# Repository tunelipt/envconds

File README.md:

# envconds
Temperature, Pressure and Humidity measurement board and software

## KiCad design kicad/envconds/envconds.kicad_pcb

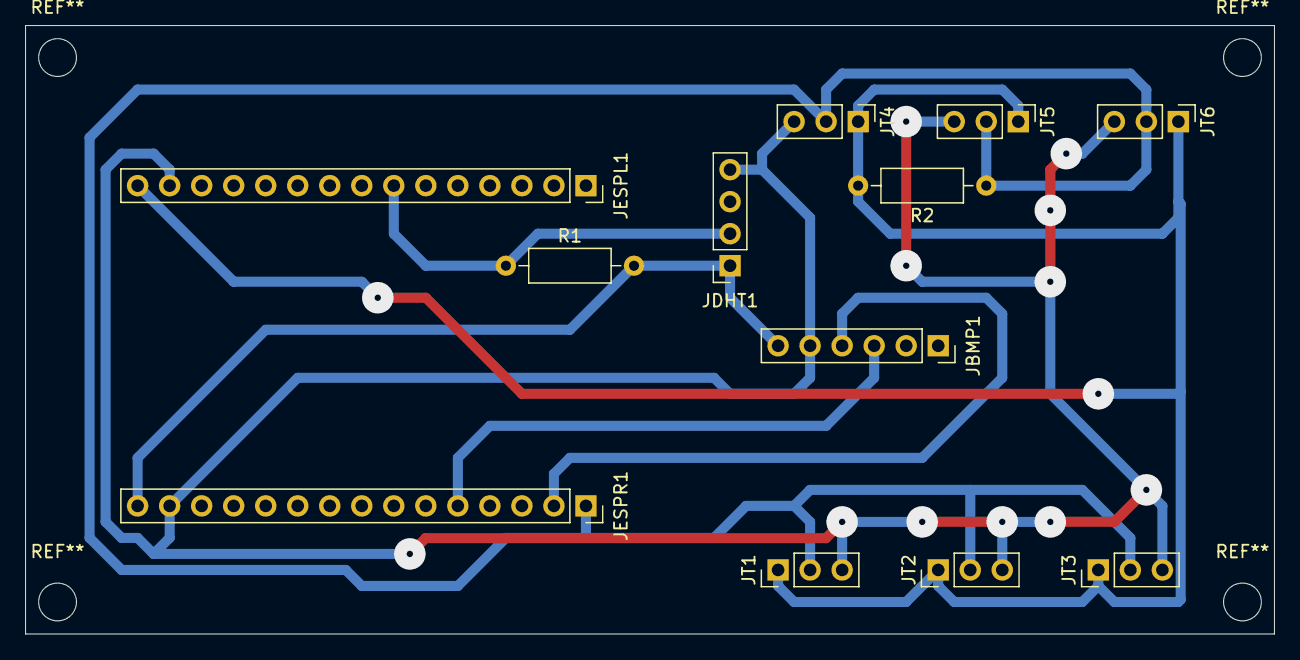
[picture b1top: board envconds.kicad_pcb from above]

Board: 2 copper layers, 99.1 x 48.3 mm, 12 parts (0 on the bottom side), 7 nets.

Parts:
JBMP1: Conn_01x06; PinSocket_1x06_P2.54mm_Vertical
JDHT1: Conn_01x04; PinSocket_1x04_P2.54mm_Vertical
JESPL1: Conn_01x15; PinSocket_1x15_P2.54mm_Vertical
JESPR1: Conn_01x15; PinSocket_1x15_P2.54mm_Vertical
JT1, JT2, JT3, JT4, JT5, JT6: Conn_01x03; PinHeader_1x03_P2.54mm_Vertical
R1, R2: 10k; R_Axial_DIN0207_L6.3mm_D2.5mm_P10.16mm_Horizontal

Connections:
/3.3V: JBMP1.6, JDHT1.1, JESPR1.15, R1.2
/5V: JESPL1.15, JT1.1, JT2.1, JT3.1, JT4.1, JT5.1, JT6.1, R2.2
/SCL: JBMP1.4, JESPR1.2
/SDA: JBMP1.3, JESPR1.5
GND: JBMP1.5, JDHT1.4, JESPL1.14, JESPR1.14, JT1.3, JT2.3, JT3.3, JT4.3, JT5.3, JT6.3
unnamed: JDHT1.2, JESPL1.7, R1.1
unnamed: JESPR1.1, JT1.2, JT2.2, JT3.2, JT4.2, JT5.2, JT6.2, R2.1

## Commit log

2021-05-06 Initial commit of the `envconds` project
    A basic board with the arduino code and a python interface is available. More testing is necessary.
2021-05-07 Working on the python interface
    I'm still experiencing problems with gibberish. I have no Idea what is going on...
2021-05-07 Changed baud rate to 9600
    I see no need for more.
2021-06-20 Added xml rpc python client.
2022-06-17 Improved funcionality of python code
2022-06-20 Added method to change the channels that are acquired.
